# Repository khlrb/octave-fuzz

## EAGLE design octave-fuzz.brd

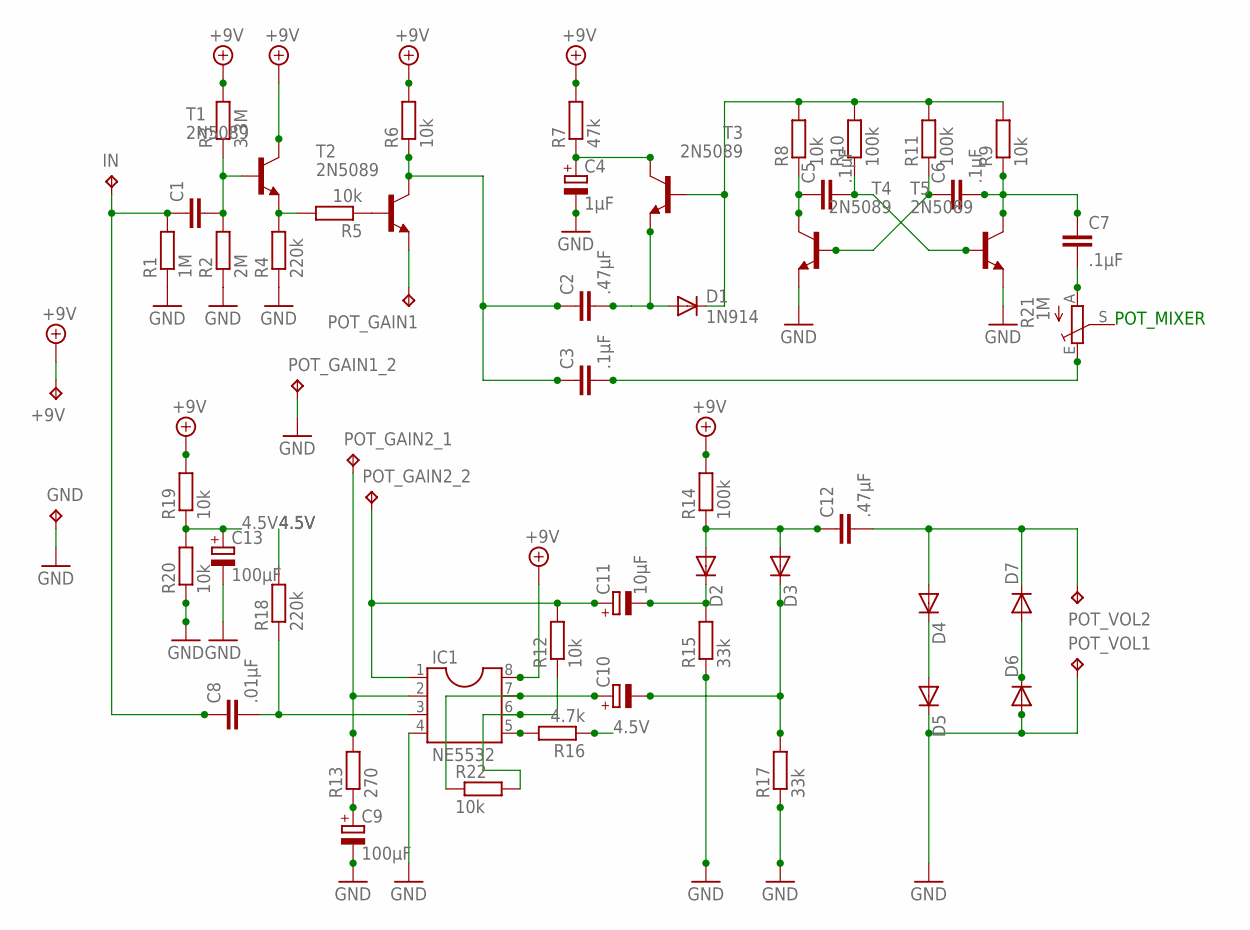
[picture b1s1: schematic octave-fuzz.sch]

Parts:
+9V: TPPAD1-20Y; P1-20Y
C1: C-EU050-025X075; C050-025X075
C2, C12: .47µF; C050-025X075
C3, C5, C6, C7: .1µF; C050-025X075
C4: 1µF; E3,5-8
C8: .01µF; C050-025X075
C9, C13: 100µF; E3,5-8
C10: CPOL-EUE3.5-8; E3,5-8
C11: 10µF; E3,5-8
D1: 1N914; D-12.5
D2, D3, D4, D5, D6, D7: DIODE-D-12.5; D-12.5
GND: TPPAD1-20Y; P1-20Y
IC1: NE5532; DIL08
IN: TPPAD1-17Y; P1-17Y
POT_GAIN1, POT_GAIN1_2, POT_GAIN2_1, POT_GAIN2_2: TPPAD1-20Y; P1-20Y
POT_VOL1, POT_VOL2: TPPAD1-20Y; P1-20Y
R1: 1M; 0207/10
R2: 2M; 0207/10
R3: 3.3M; 0207/10
R4, R18: 220k; 0207/10
R5, R6, R8, R9, R12, R19, R20, R22: 10k; 0207/10
R7: 47k; 0207/10
R10, R11, R14: 100k; 0207/10
R13: 270; 0207/10
R15, R17: 33k; 0207/10
R16: 4.7k; 0207/10
R21: 1M; CA9V
T1, T2, T3, T4, T5: 2N5089; TO92

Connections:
4.5V: C13.+, R16.1, R18.2, R19.1, R20.2
+9V: +9V.TP, IC1.8, R3.2, R6.2, R7.2, R14.2, R19.2, T1.1 (C)
GND: C4.-, C9.-, C13.-, D5.C, D6.A, GND.TP, IC1.4, POT_GAIN1_2.TP, POT_VOL1.TP, R1.1, R2.1, R4.1, R15.1, R17.1, R20.1, T4.3 (E), T5.3 (E)
unnamed: C1.1, C8.1, IN.TP, R1.2
unnamed: C1.2, R2.2, R3.1, T1.2 (B)
unnamed: R4.2, R5.2, T1.3 (E)
unnamed: R5.1, T2.2 (B)
unnamed: C2.1, C3.1, R6.1, T2.1 (C)
unnamed: POT_GAIN1.TP, T2.3 (E)
unnamed: C4.+, R7.1, T3.1 (C)
unnamed: C2.2, D1.A, T3.3 (E)
unnamed: C5.1, R8.1, T4.1 (C)
unnamed: C8.2, IC1.3, R18.1
unnamed: C3.2, R21.E
unnamed: C7.2, R21.A
unnamed: C6.1, R11.1, T4.2 (B)
unnamed: D1.C, R8.2, R9.2, R10.2, R11.2, T3.2 (B)
unnamed: IC1.2, POT_GAIN2_1.TP, R13.2
unnamed: C9.+, R13.1
unnamed: C11.+, IC1.1, POT_GAIN2_2.TP, R12.2
unnamed: IC1.6, R12.1, R22.2
unnamed: C10.+, IC1.7, R22.1
unnamed: IC1.5, R16.2
unnamed: D4.C, D5.A
unnamed: D6.C, D7.A
unnamed: C12.2, D4.A, D7.C, POT_VOL2.TP
unnamed: C10.-, D3.C, R17.2
unnamed: C12.1, D2.A, D3.A, R14.1
unnamed: C11.-, D2.C, R15.2
unnamed: C6.2, C7.1, R9.1, T5.1 (C)
unnamed: C5.2, R10.1, T5.2 (B)

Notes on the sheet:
POT_MIXER

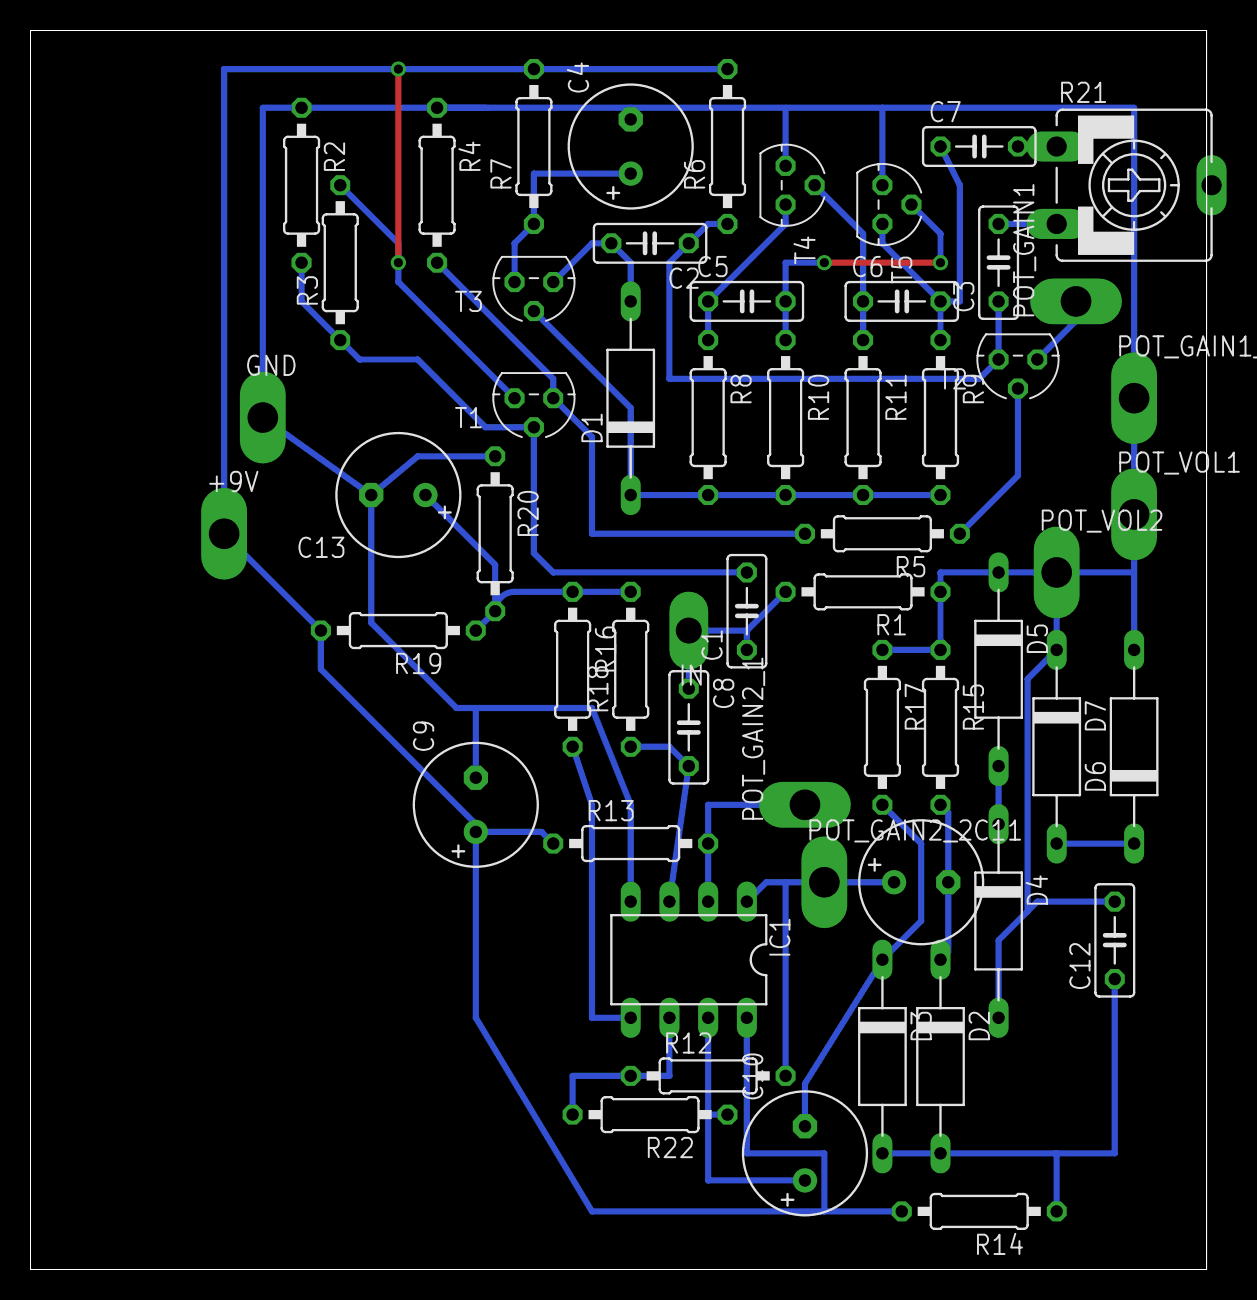
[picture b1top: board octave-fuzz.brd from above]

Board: 2 copper layers, 77.1 x 81.3 mm, 57 parts (0 on the bottom side), 31 nets.

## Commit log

2016-10-10 add .gitignore
2016-10-10 optimized layout
2016-10-14 improved pcb layout
2016-10-14 added a missing resistor and edited component values
